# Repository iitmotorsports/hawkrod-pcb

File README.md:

View this project on [CADLAB.io](https://cadlab.io/project/25936). 

# hawkrod-pcb
The assets for the various PCBs and components of HawkRod

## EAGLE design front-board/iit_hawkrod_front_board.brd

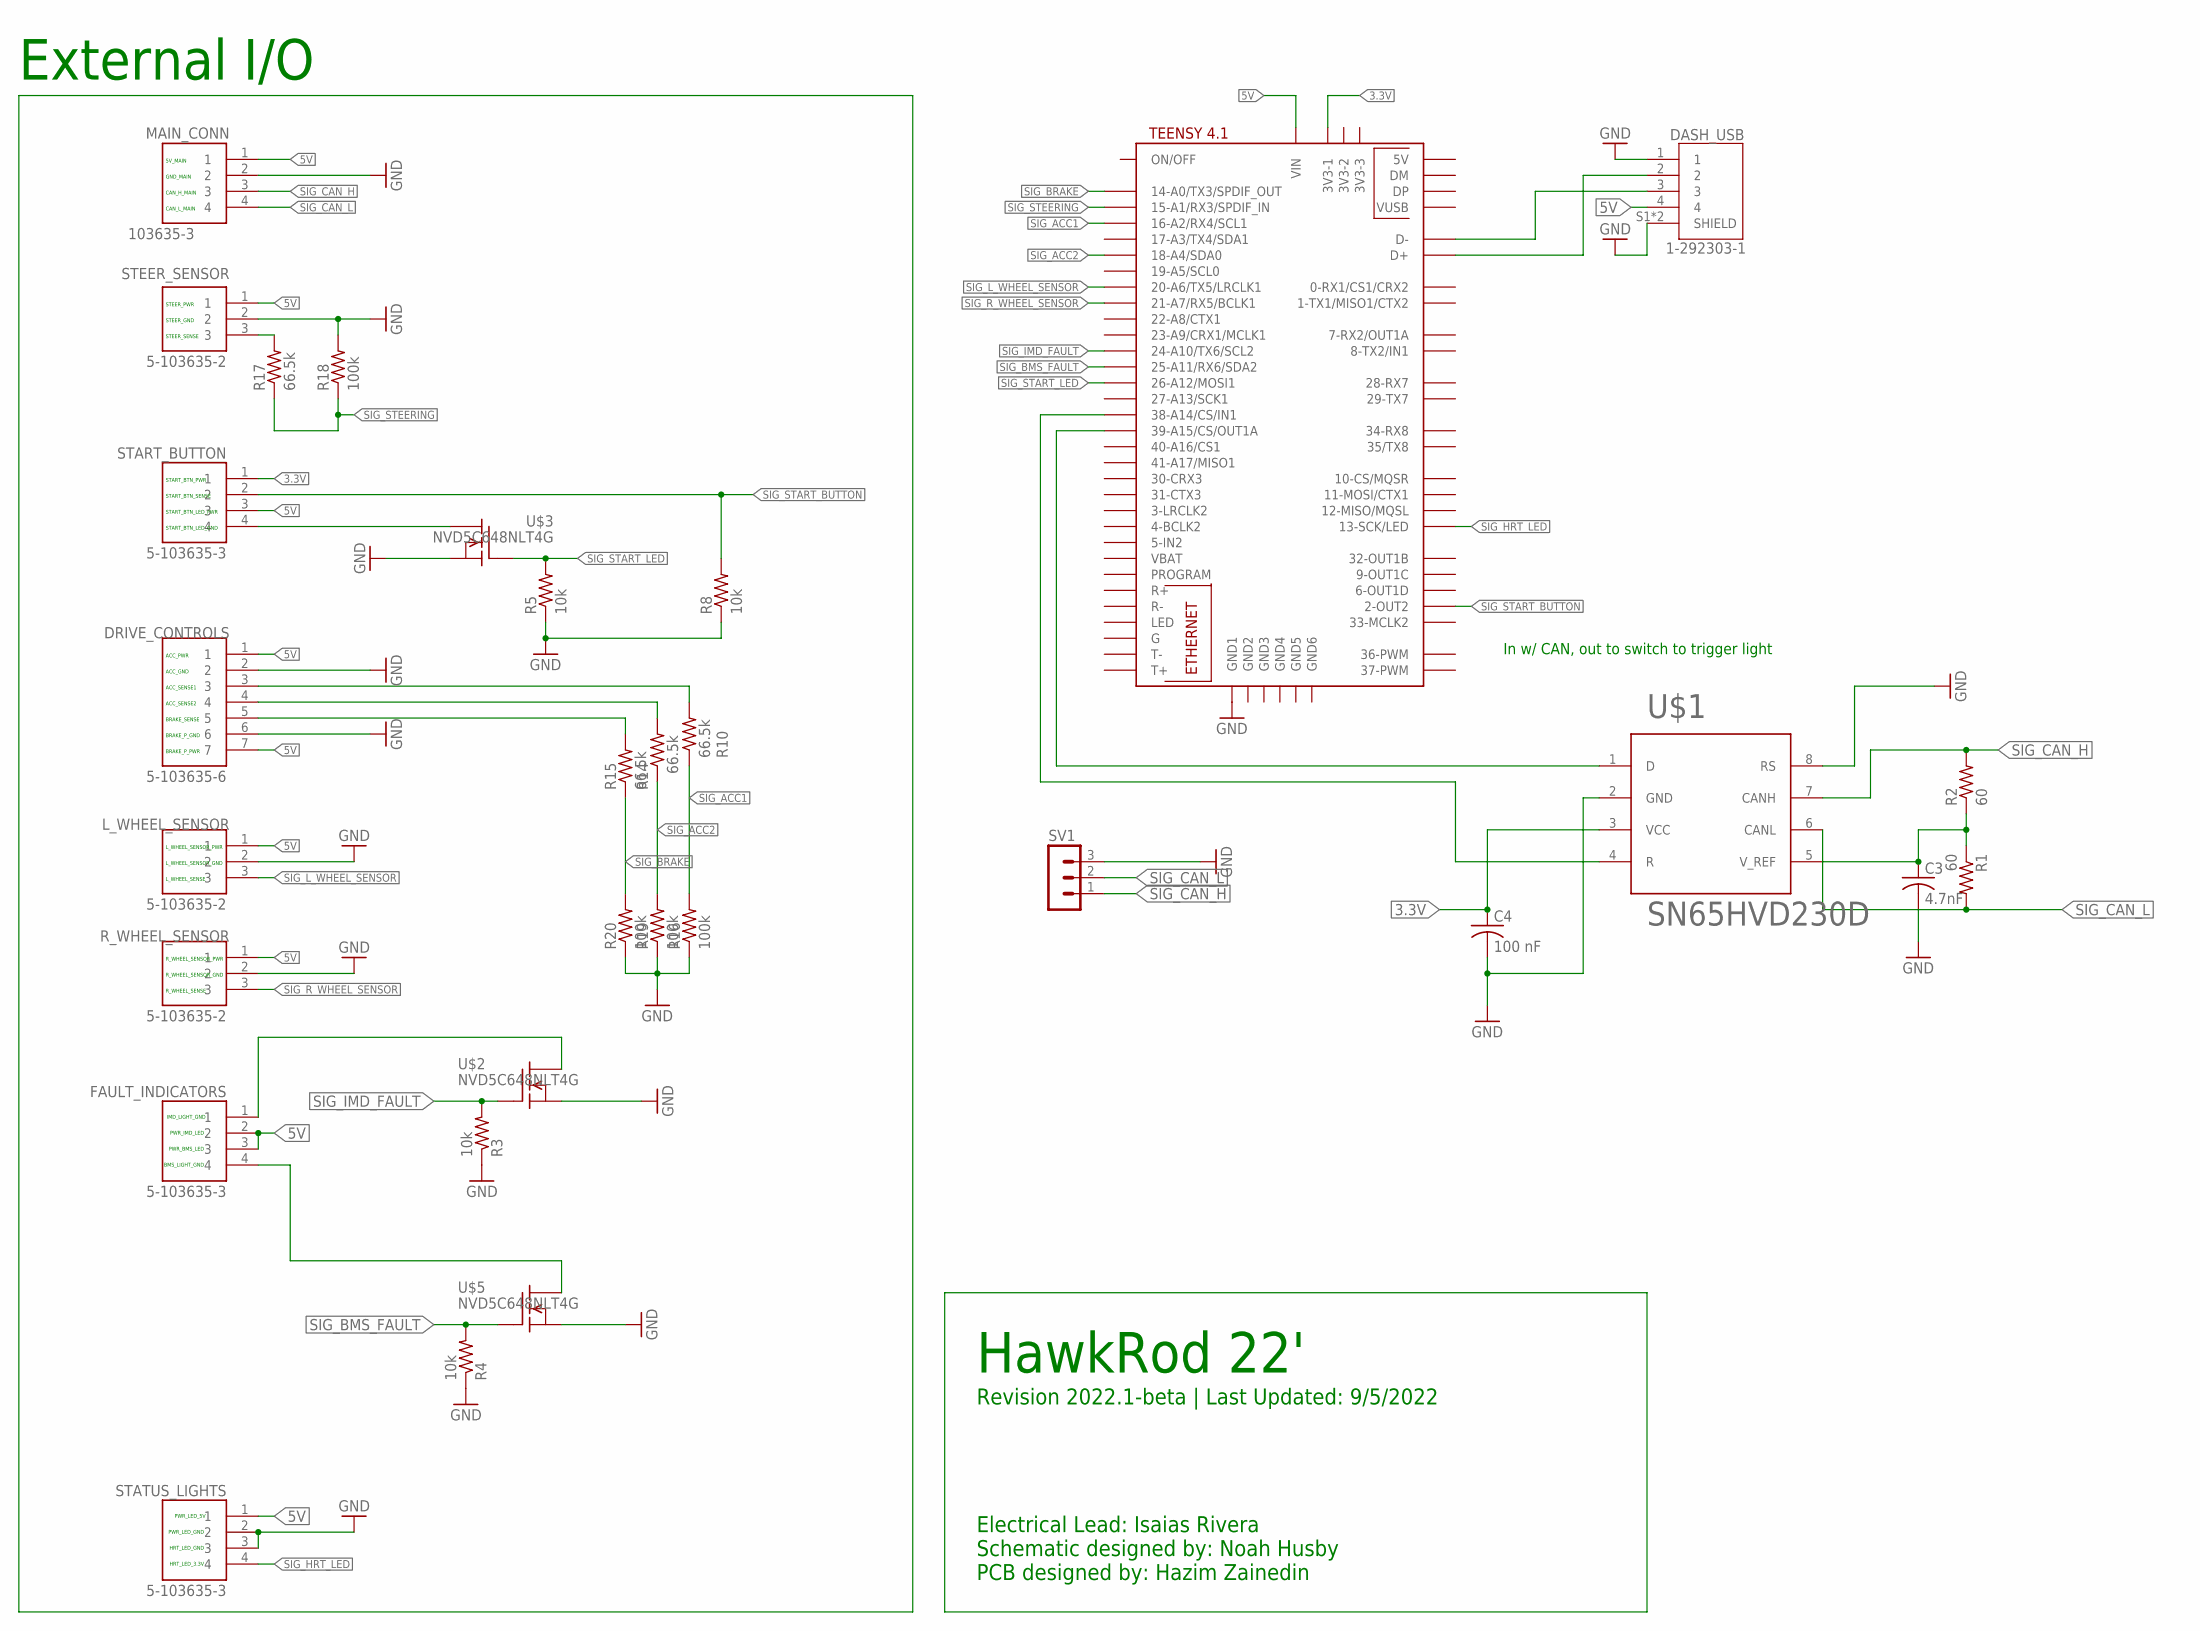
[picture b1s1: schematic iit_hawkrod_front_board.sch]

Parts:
C3: 4.7nF; C1206
C4: 100 nF; C1206
DASH_USB: 1-292303-1; TE_1-292303-1
DRIVE_CONTROLS: 5-103635-6; TE_5-103635-6
FAULT_INDICATORS: 5-103635-3; TE_5-103635-3
L_WHEEL_SENSOR: 5-103635-2; TE_5-103635-2
MAIN_CONN: 103635-3; TE_103635-3
R1, R2: 60; R1206
R3, R4, R5, R8: 10k; R1206
R10, R14, R15, R17: 66.5k; R1206
R16, R18, R19, R20: 100k; R1206
R_WHEEL_SENSOR: 5-103635-2; TE_5-103635-2
START_BUTTON: 5-103635-3; TE_5-103635-3
STATUS_LIGHTS: 5-103635-3; TE_5-103635-3
STEER_SENSOR: 5-103635-2; TE_5-103635-2
SV1: MA03-1
U$1: SN65HVD230D; R-PDSO-8
U$2, U$3, U$5: NVD5C648NLT4G; DPAK
U$6: TEENSY41

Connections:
3.3V: C4.1, START_BUTTON.1, U$1.3 (VCC), U$6.3V3-1
5V: DASH_USB.4, DRIVE_CONTROLS.1, DRIVE_CONTROLS.7, FAULT_INDICATORS.2, FAULT_INDICATORS.3, L_WHEEL_SENSOR.1, MAIN_CONN.1, R_WHEEL_SENSOR.1, START_BUTTON.3, STATUS_LIGHTS.1, STEER_SENSOR.1, U$6.VIN
GND: C3.2, C4.2, DASH_USB.1, DASH_USB.S1 (SHIELD), DASH_USB.S2 (SHIELD), DRIVE_CONTROLS.2, DRIVE_CONTROLS.6, L_WHEEL_SENSOR.2, MAIN_CONN.2, R3.1, R4.1, R5.1, R8.1, R16.1, R18.2, R19.1, R20.1, R_WHEEL_SENSOR.2, STATUS_LIGHTS.2, STATUS_LIGHTS.3, STEER_SENSOR.2, SV1.3, U$1.2 (GND), U$1.8 (RS), U$2.3 (S), U$3.3 (S), U$5.3 (S), U$6.GND1
unnamed: U$1.1 (D), U$6.39-A15/CS/OUT1A
unnamed: R2.2, U$1.7 (CANH)
unnamed: C3.1, R1.1, R2.1, U$1.5 (V_REF)
unnamed: FAULT_INDICATORS.1, U$2.4 (D)
unnamed: R1.2, U$1.6 (CANL)
unnamed: U$1.4 (R), U$6.38-A14/CS/IN1
unnamed: START_BUTTON.4, U$3.4 (D)
unnamed: FAULT_INDICATORS.4, U$5.4 (D)
unnamed: DRIVE_CONTROLS.3, R10.2
unnamed: DRIVE_CONTROLS.4, R14.2
unnamed: DASH_USB.3, U$6.D-
unnamed: DRIVE_CONTROLS.5, R15.2
unnamed: R17.2, STEER_SENSOR.3
unnamed: DASH_USB.2, U$6.D+
SIG_ACC1: R10.1, R16.2, U$6.16-A2/RX4/SCL1
SIG_ACC2: R14.1, R19.2, U$6.18-A4/SDA0
SIG_BMS_FAULT: R4.2, U$5.1 (G), U$6.25-A11/RX6/SDA2
SIG_BRAKE: R15.1, R20.2, U$6.14-A0/TX3/SPDIF_OUT
SIG_CAN_H: MAIN_CONN.3, SV1.1
SIG_CAN_L: MAIN_CONN.4, SV1.2
SIG_HRT_LED: STATUS_LIGHTS.4, U$6.13-SCK/LED
SIG_IMD_FAULT: R3.2, U$2.1 (G), U$6.24-A10/TX6/SCL2
SIG_L_WHEEL_SENSOR: L_WHEEL_SENSOR.3, U$6.20-A6/TX5/LRCLK1
SIG_R_WHEEL_SENSOR: R_WHEEL_SENSOR.3, U$6.21-A7/RX5/BCLK1
SIG_START_BUTTON: R8.2, START_BUTTON.2, U$6.2-OUT2
SIG_START_LED: R5.2, U$3.1 (G), U$6.26-A12/MOSI1
SIG_STEERING: R17.1, R18.1, U$6.15-A1/RX3/SPDIF_IN

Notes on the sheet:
PWR_IMD_LED
PWR_BMS_LED
IMD_LIGHT_GND
BMS_LIGHT_GND
In w/ CAN, out to switch to trigger light
GND_MAIN
5V_MAIN
CAN_H_MAIN
CAN_L_MAIN
STEER_PWR
STEER_GND
STEER_SENSE
START_BTN_PWR
START_BTN_LED_PWR
START_BTN_SENSE
START_BTN_LED_GND
ACC_PWR
ACC_GND
ACC_SENSE1
ACC_SENSE2
BRAKE_SENSE
BRAKE_P_GND
BRAKE_P_PWR
L_WHEEL_SENSOR_PWR
L_WHEEL_SENSOR_GND
L_WHEEL_SENSE
R_WHEEL_SENSOR_PWR
R_WHEEL_SENSOR_GND
R_WHEEL_SENSE
External I/O
HawkRod 22'
Revision 2022.1-beta | Last Updated: 9/5/2022
Electrical Lead: Isaias Rivera Schematic designed by: Noah Husby PCB designed by: Hazim Zainedin
PWR_LED_GND
HRT_LED_GND
PWR_LED_5V
HRT_LED_3.3V

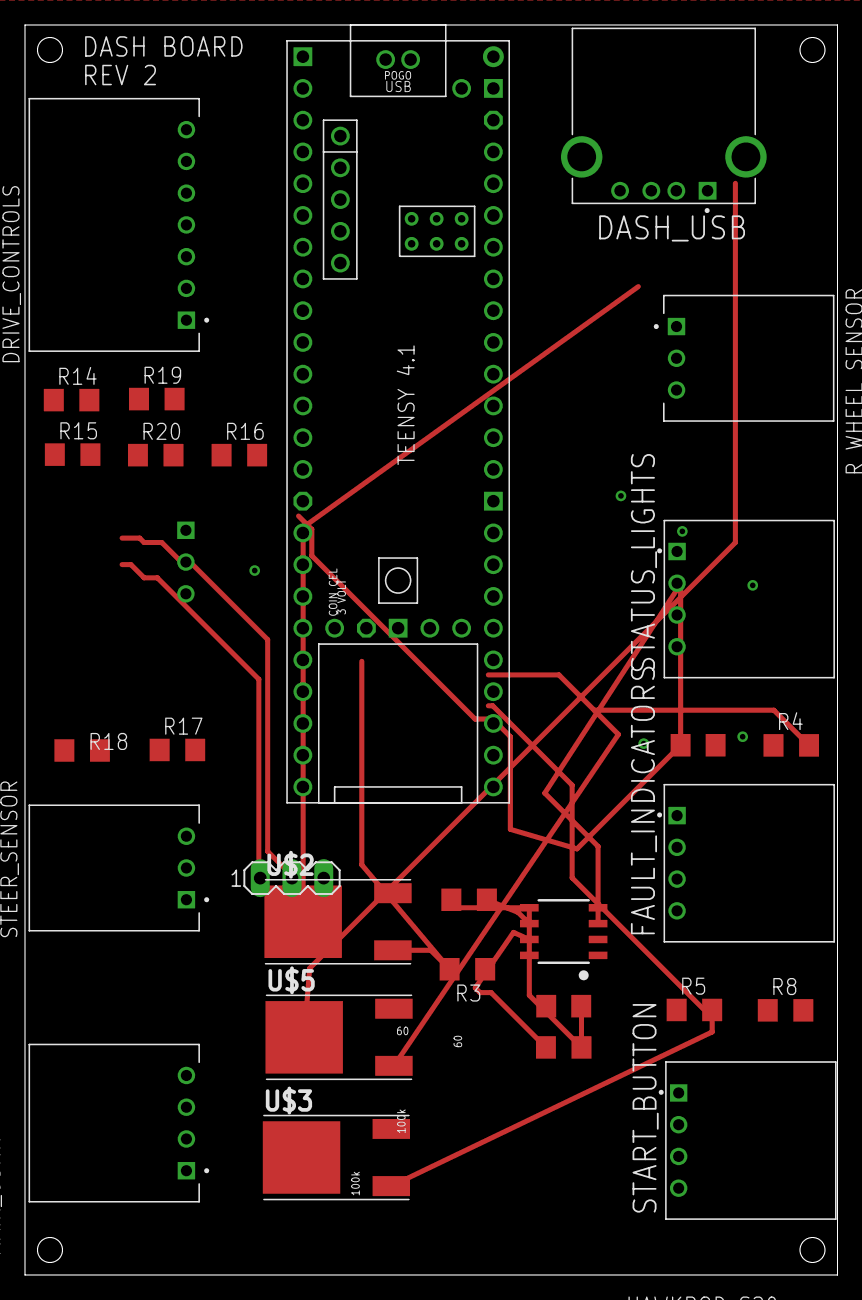
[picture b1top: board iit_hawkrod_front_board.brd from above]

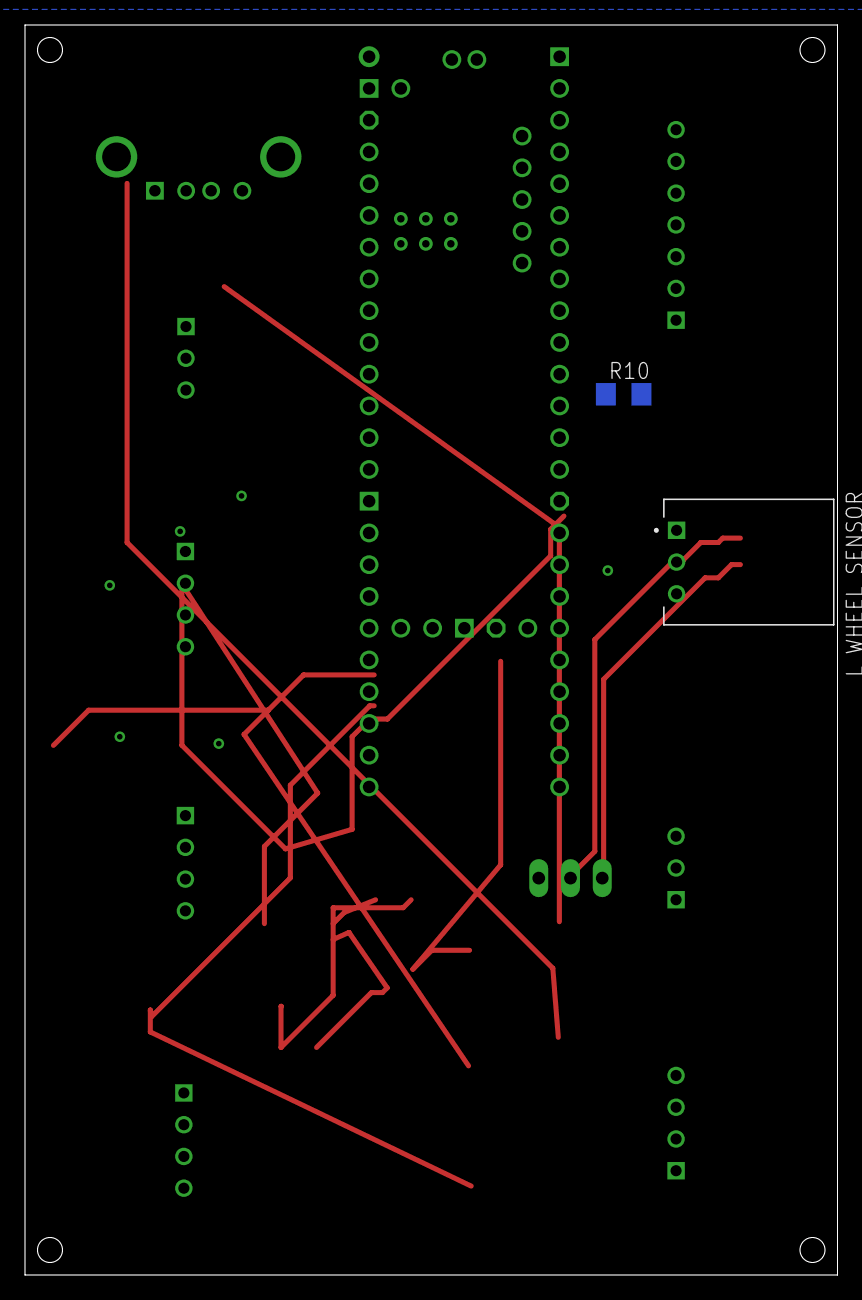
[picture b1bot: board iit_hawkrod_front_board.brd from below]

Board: 2 copper layers, 65.0 x 100.0 mm, 31 parts (2 on the bottom side), 30 nets.

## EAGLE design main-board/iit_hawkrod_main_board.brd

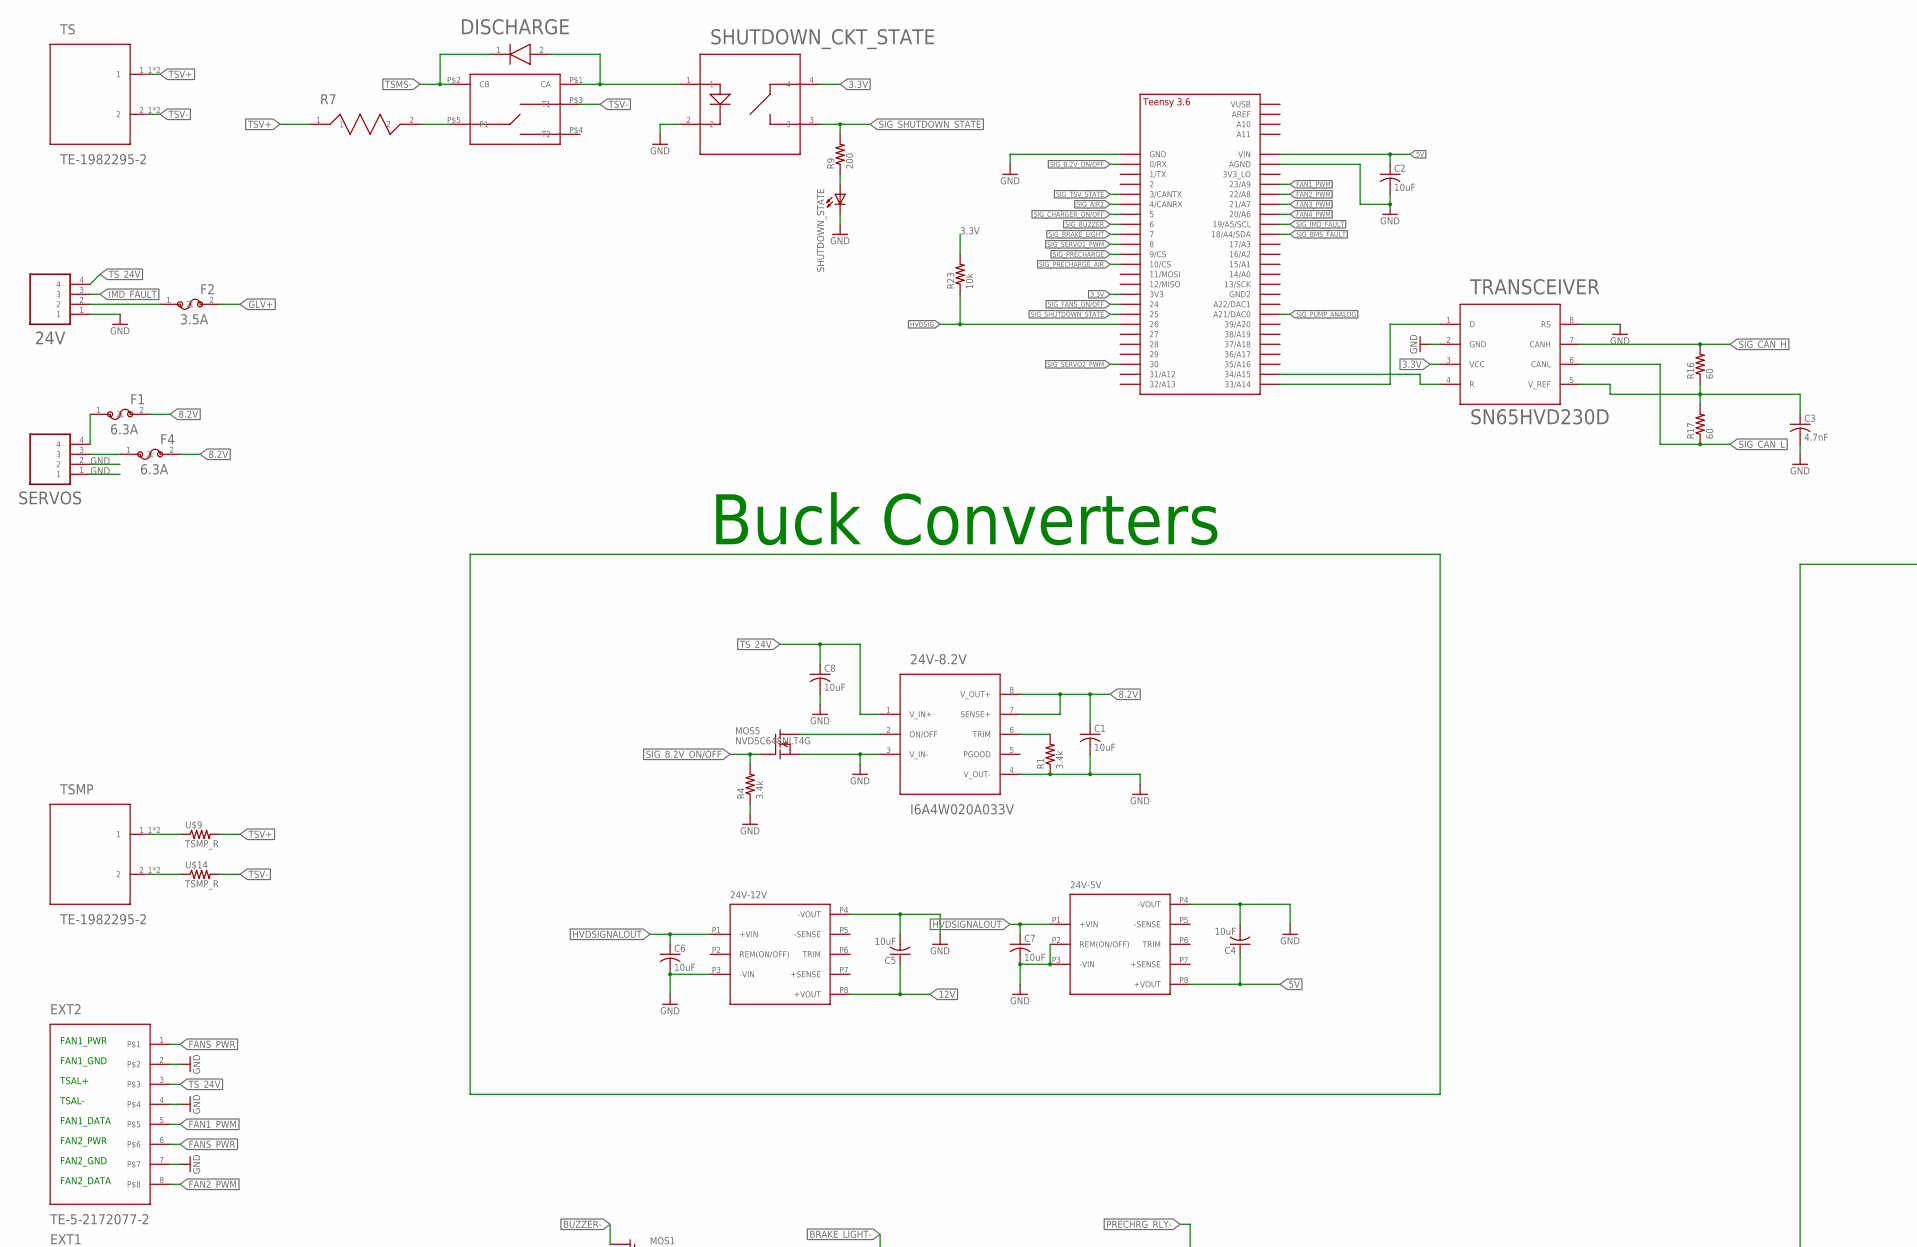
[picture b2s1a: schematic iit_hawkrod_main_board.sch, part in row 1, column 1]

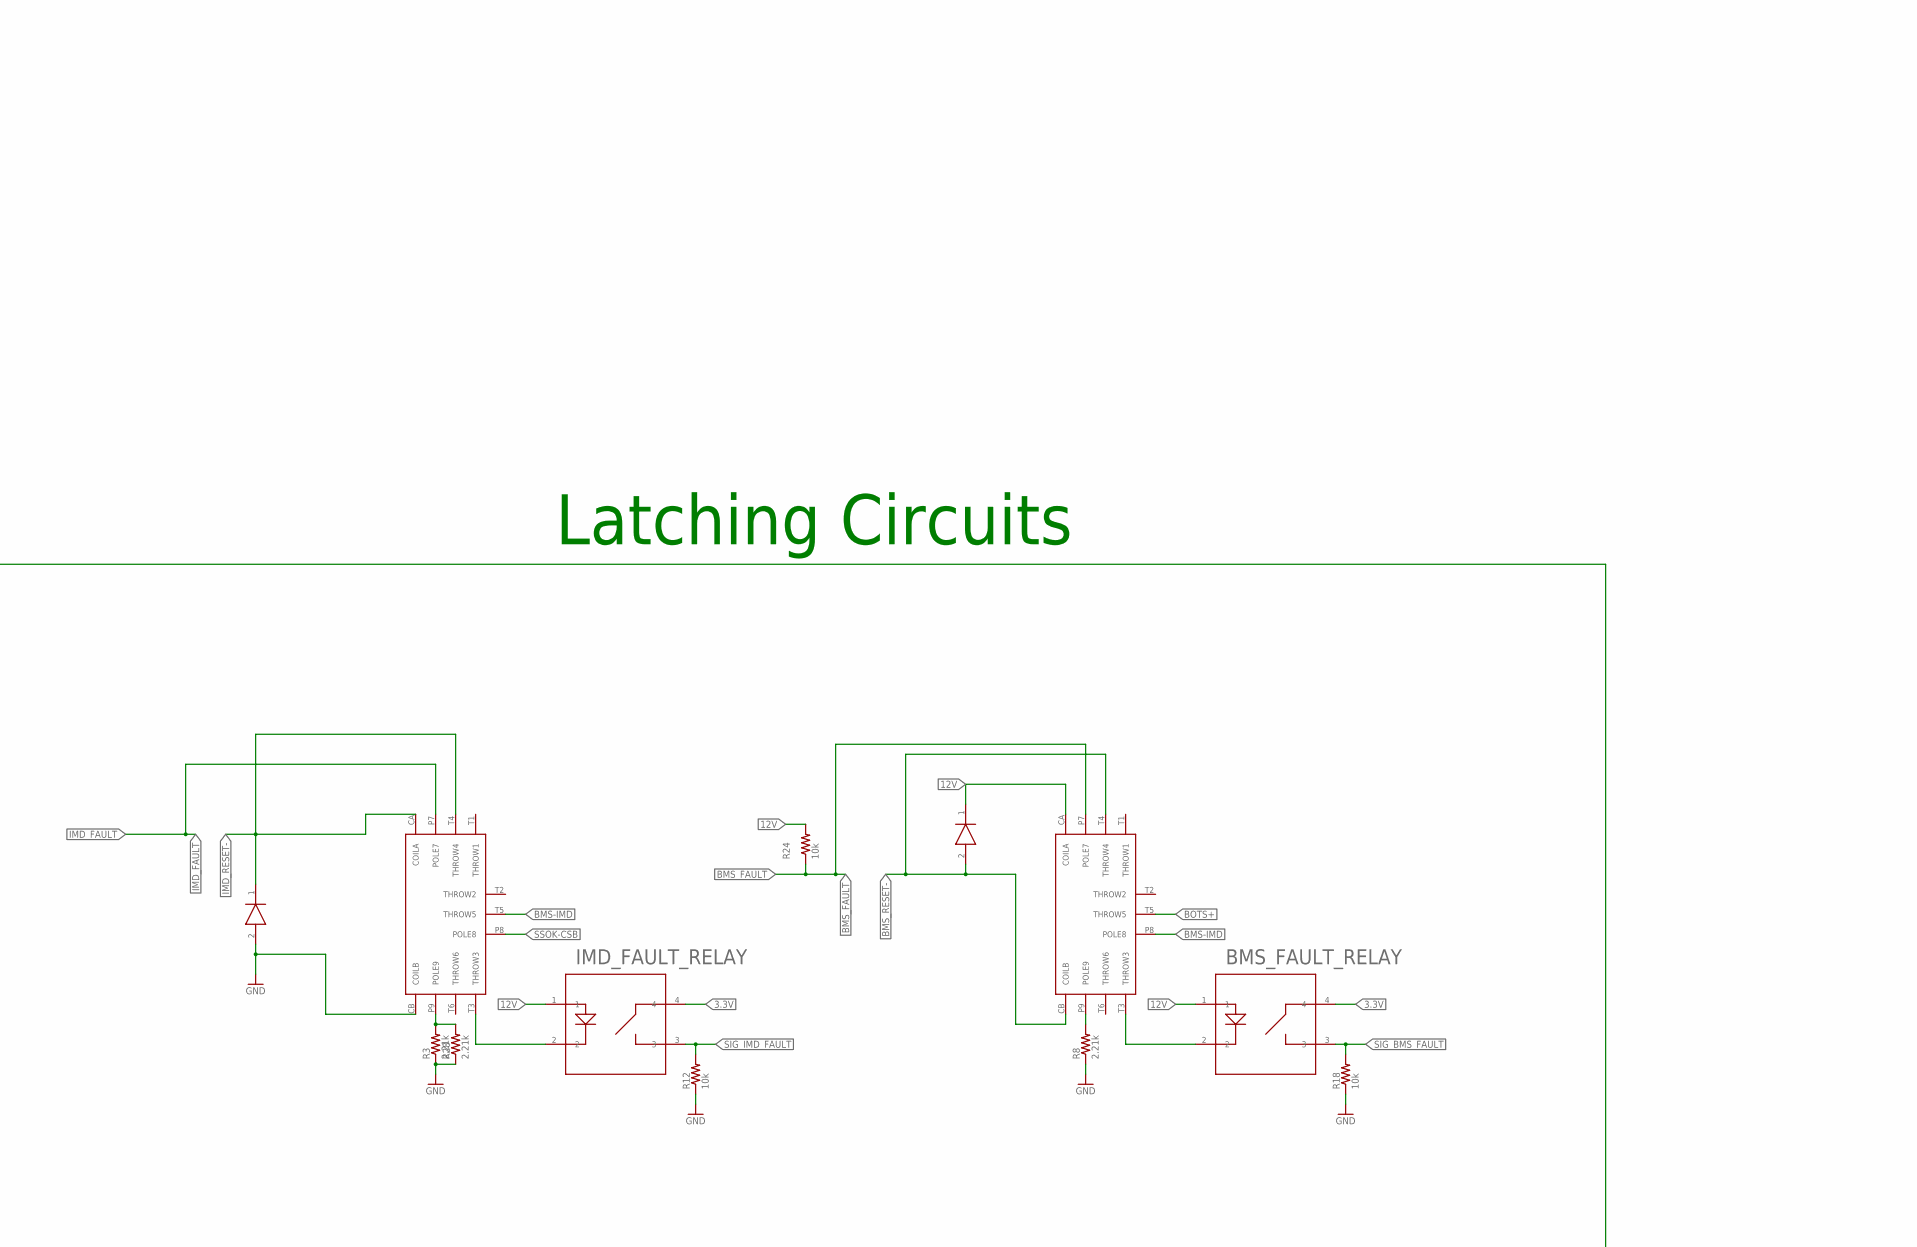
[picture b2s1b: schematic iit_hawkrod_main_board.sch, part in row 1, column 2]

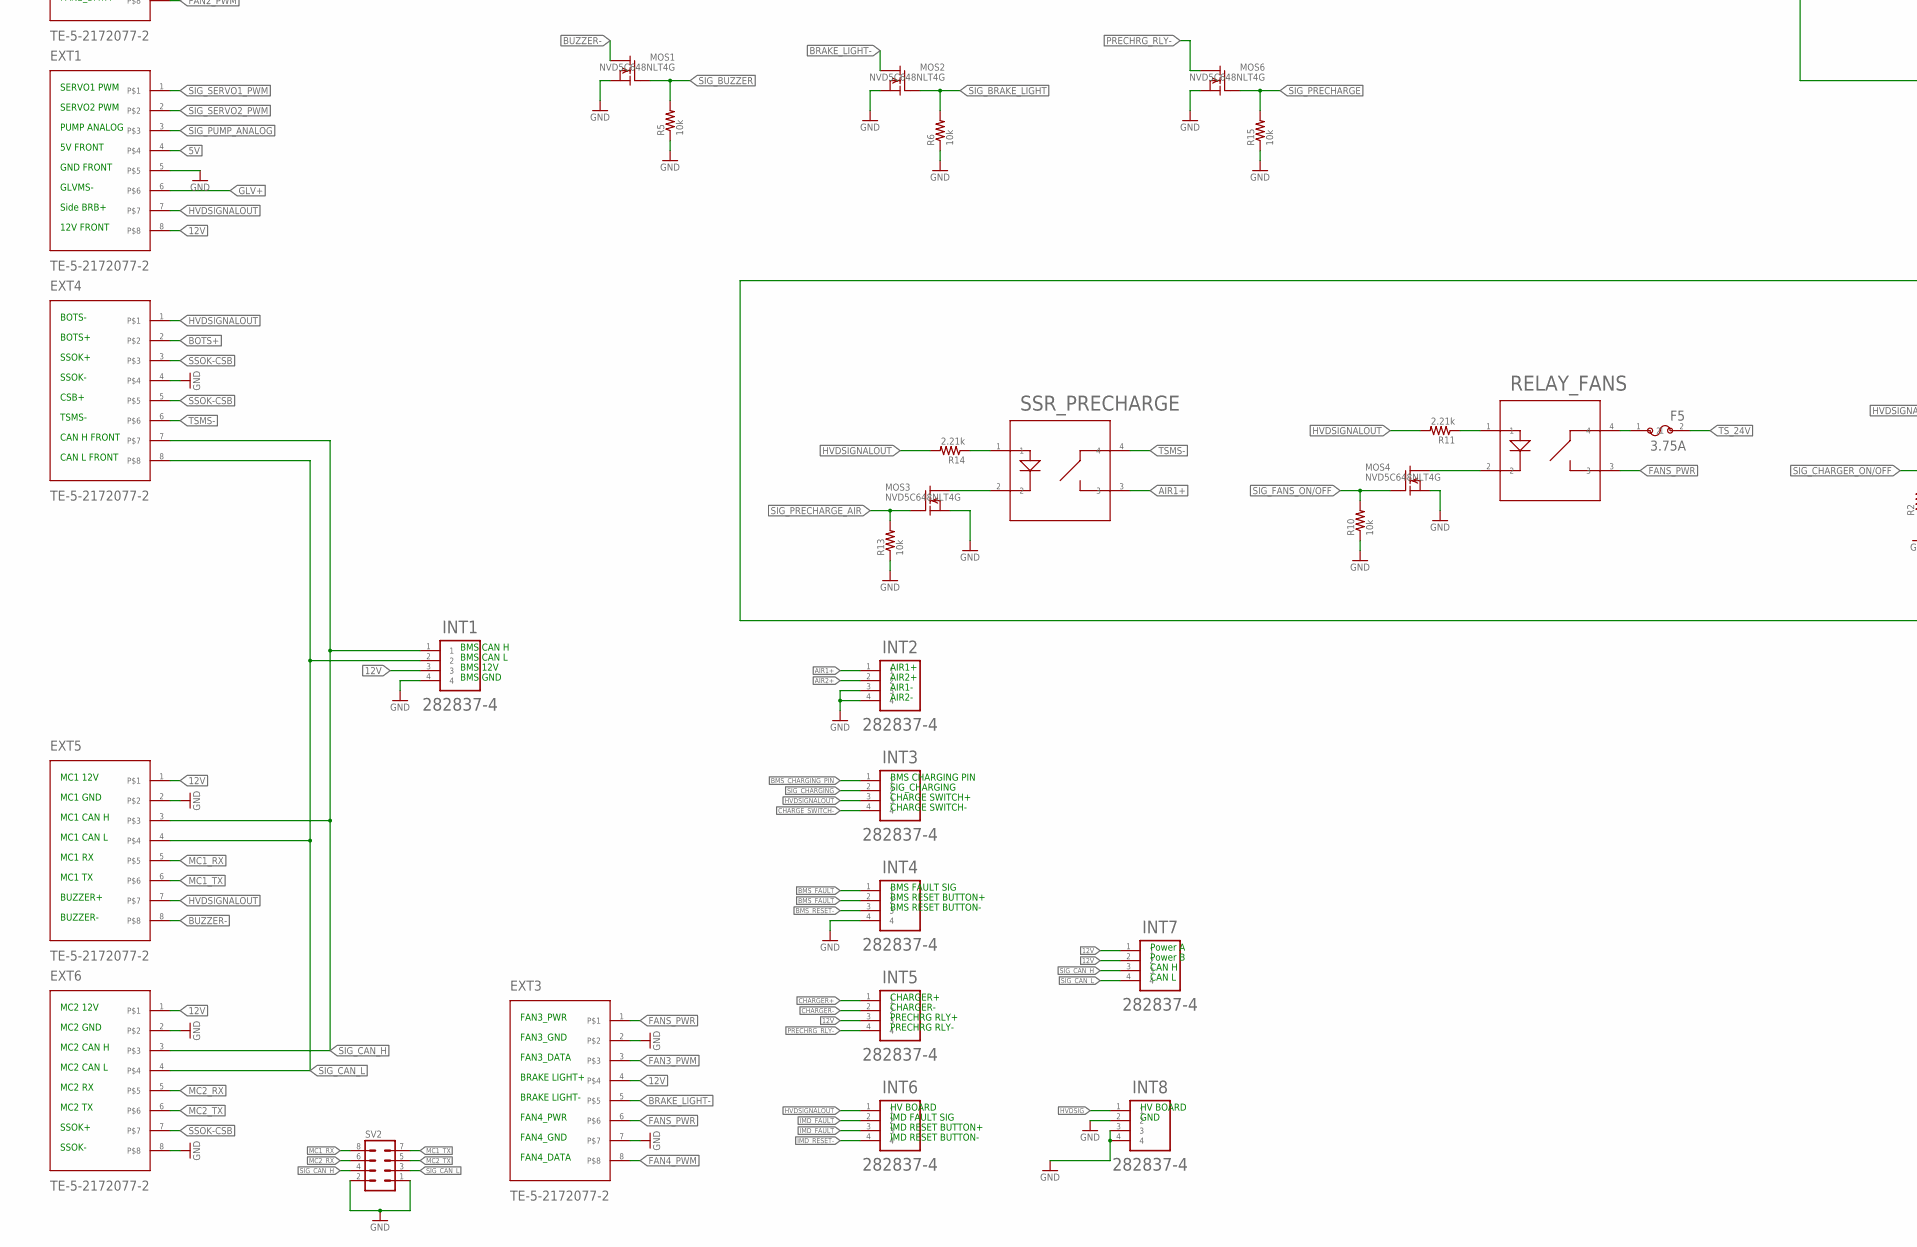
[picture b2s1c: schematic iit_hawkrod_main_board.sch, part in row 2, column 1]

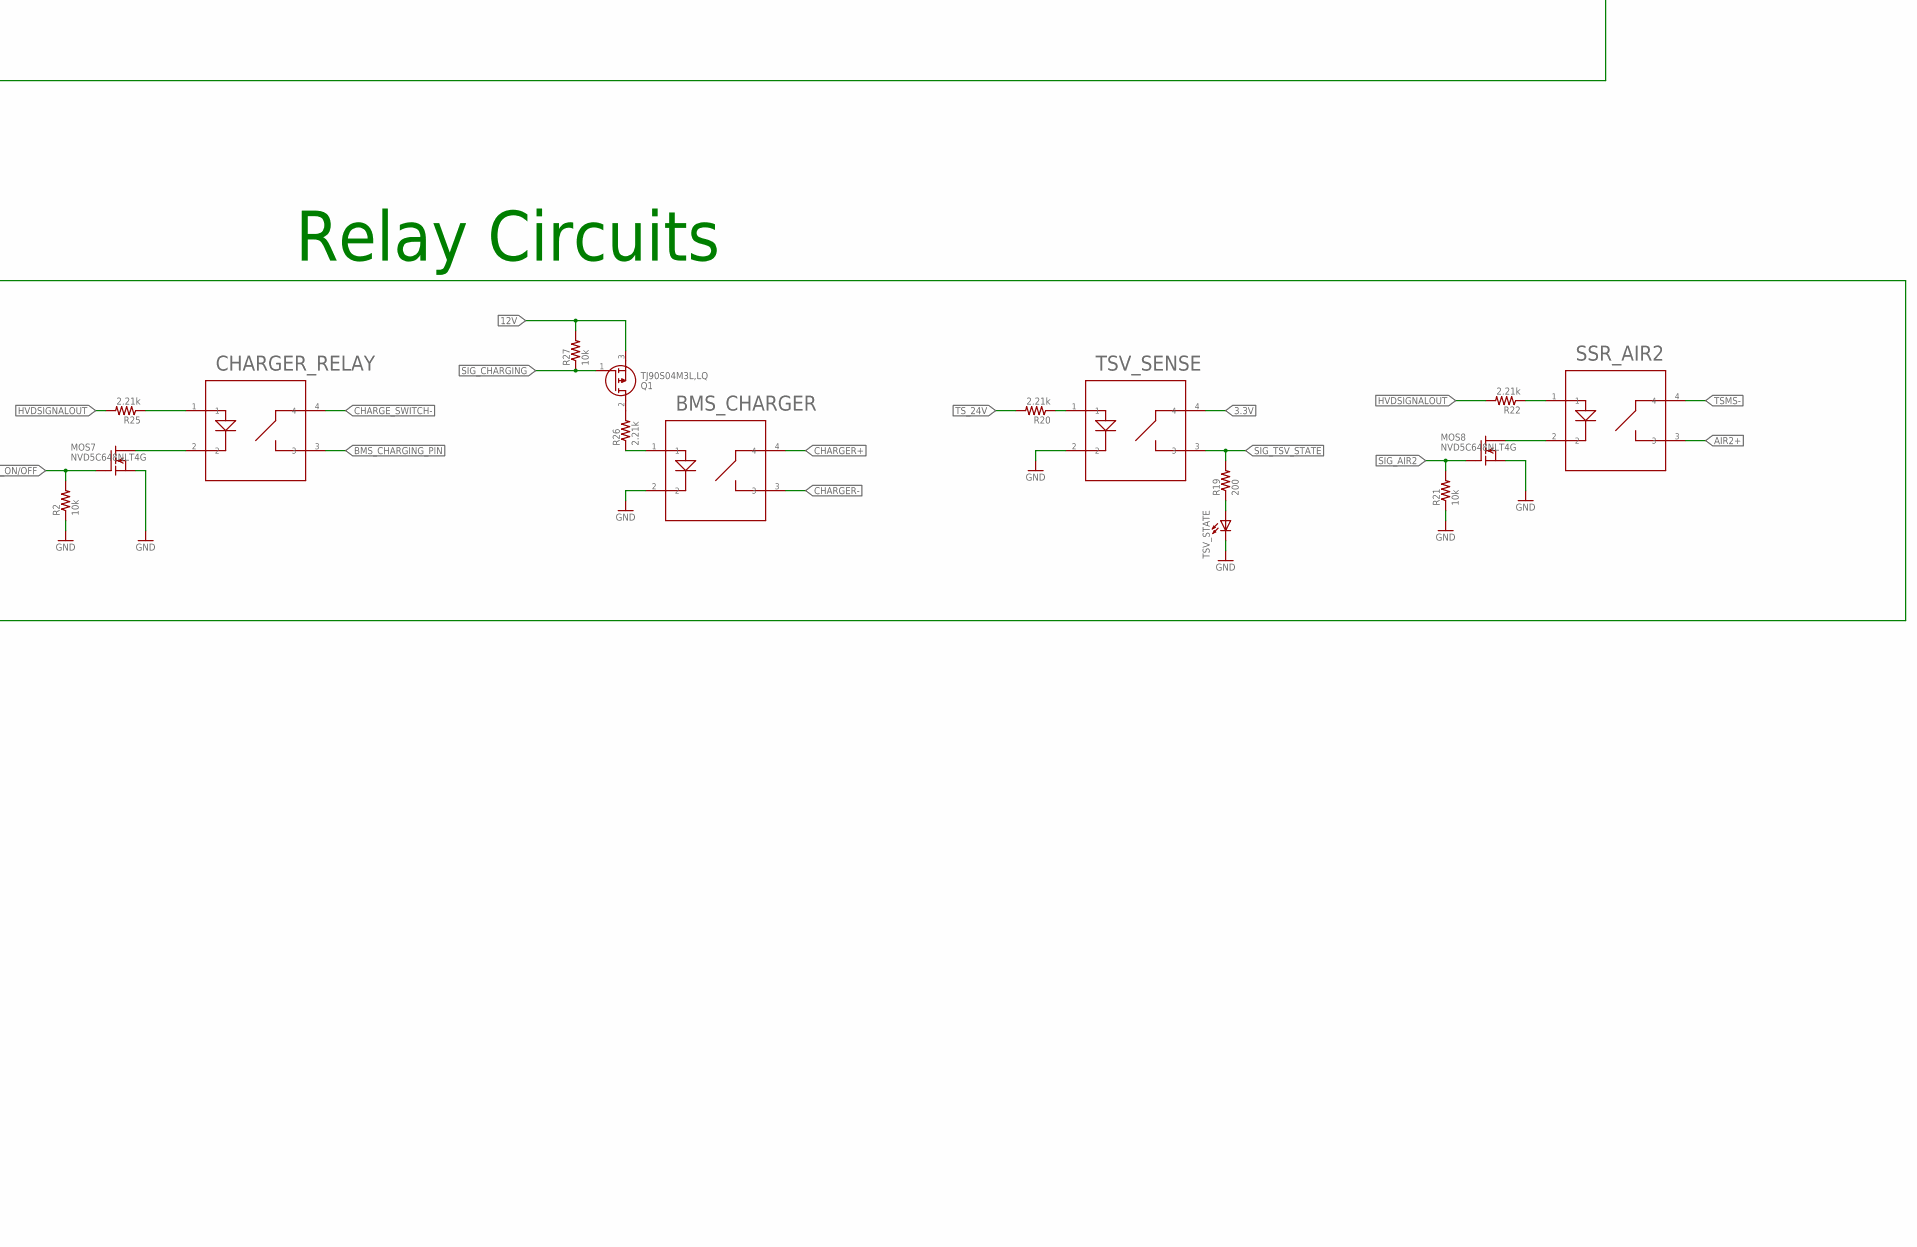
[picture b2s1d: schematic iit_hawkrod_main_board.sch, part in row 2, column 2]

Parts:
24V: 282837-4; TE_282837-4
24V-5V, 24V-12V: IRS-5/10-Q12NF-C
24V-8.2V: I6A4W020A033V
BMS_CHARGER: G3VM-61GR2; SOP4
BMS_FAULT_RELAY: G3VM-61GR2; SOP4
C1, C2, C4, C5, C6, C7, C8: 10uF; C1206
C3: 4.7nF; C1206
CHARGER_RELAY: G3VM-61GR2; SOP4
EXT1, EXT2, EXT3, EXT4, EXT5, EXT6: TE-5-2172077-2
F1, F4: 6.3A; SMD_FUSE_HOLDER
F2: 3.5A; SMD_FUSE_HOLDER
F5: 3.75A; SMD_FUSE_HOLDER
IMD_FAULT_RELAY: G3VM-61GR2; SOP4
INT1, INT2, INT3, INT4, INT5, INT6, INT7, INT8: 282837-4; TE_282837-4
MOS1, MOS2, MOS3, MOS4, MOS5, MOS6, MOS7, MOS8: NVD5C648NLT4G; DPAK
Q1: TJ90S04M3L,LQ; TJ90S04M3LLQ
R1, R4: 3.4k; R1206
R2, R10, R27: 10k; R1206
R3, R8, R11, R14, R20, R22, R25, R26, R28: 2.21k; R1206
R5, R6, R12, R13, R15, R18, R21, R23, R24: 10k; M1206
R7: HSA501K0J
R9, R19: 200; M1206
R16, R17: 60; R1206
RELAY_FANS: G3VM-61GR2; SOP4
SERVOS: 282837-4; TE_282837-4
SHUTDOWN_CKT_STATE: G3VM-61GR2; SOP4
SHUTDOWN_STATE: LEDCHIP-LED0805; CHIP-LED0805
SSR_AIR2: G3VM-61GR2; SOP4
SSR_PRECHARGE: G3VM-61GR2; SOP4
SV2: MA04-2
TEENSY_3.6: TEENSY_3.5/3.6_BASIC
TRANSCEIVER: SN65HVD230D; R-PDSO-8
TS: TE-1982295-2
TSMP: TE-1982295-2
TSV_SENSE: G3VM-61GR2; SOP4
TSV_STATE: LEDCHIP-LED0805; CHIP-LED0805
U$1: G2RL-1-HA
U$3, U$4, U$5: CS1M-E3/H; DO-214AC
U$6, U$7: 27E046_RELAY_MOUNT
U$9, U$14: TSMP_R

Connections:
3.3V: BMS_FAULT_RELAY.4, IMD_FAULT_RELAY.4, R23.2, SHUTDOWN_CKT_STATE.4, TEENSY_3.6.3V3, TRANSCEIVER.3 (VCC), TSV_SENSE.4
5V: 24V-5V.P8 (+VOUT), C2.1, C4.1, EXT1.4, TEENSY_3.6.VIN
8.2V: 24V-8.2V.7 (SENSE+), 24V-8.2V.8 (V_OUT+), C1.1, F1.2, F4.2
12V: 24V-12V.P8 (+VOUT), BMS_FAULT_RELAY.1, C5.1, EXT1.8, EXT3.4, EXT5.1, EXT6.1, IMD_FAULT_RELAY.1, INT1.3, INT5.3, INT7.1, INT7.2, Q1.3 (S), R24.2, R27.2, U$5.1 (2), U$7.CA (COILA)
AIR1+: INT2.1, SSR_PRECHARGE.3
AIR2+: INT2.2, SSR_AIR2.3
BMS-IMD: U$6.T5 (THROW5), U$7.P8 (POLE8)
BMS_CHARGING_PIN: CHARGER_RELAY.3, INT3.1
BMS_FAULT: INT4.1, INT4.2, R24.1, U$7.P7 (POLE7)
BMS_RESET-: INT4.3, U$5.2 (1), U$7.CB (COILB), U$7.T4 (THROW4)
BOTS+: EXT4.2, U$7.T5 (THROW5)
BRAKE_LIGHT-: EXT3.5, MOS2.4 (D)
BUZZER-: EXT5.8, MOS1.4 (D)
CHARGER+: BMS_CHARGER.4, INT5.1
CHARGER-: BMS_CHARGER.3, INT5.2
CHARGE_SWITCH-: CHARGER_RELAY.4, INT3.4
FAN1_PWM: EXT2.5, TEENSY_3.6.23/A9
FAN2_PWM: EXT2.8, TEENSY_3.6.22/A8
FAN3_PWM: EXT3.3, TEENSY_3.6.21/A7
FAN4_PWM: EXT3.8, TEENSY_3.6.20/A6
FANS_PWR: EXT2.1, EXT2.6, EXT3.1, EXT3.6, RELAY_FANS.3
GLV+: EXT1.6, F2.2
GND: 24V.1, 24V-5V.P2 (REM(ON/OFF)), 24V-5V.P3 (-VIN), 24V-5V.P4 (-VOUT), 24V-8.2V.3 (V_IN-), 24V-8.2V.4 (V_OUT-), 24V-12V.P3 (-VIN), 24V-12V.P4 (-VOUT), BMS_CHARGER.2, C1.2, C2.2, C3.2, C4.2, C5.2, C6.2, C7.2, C8.2, EXT1.5, EXT2.2, EXT2.4, EXT2.7, EXT3.2, EXT3.7, EXT4.4, EXT5.2, EXT6.2, EXT6.8, INT1.4, INT2.3, INT2.4, INT4.4, INT8.2, INT8.3, INT8.4, MOS1.3 (S), MOS2.3 (S), MOS3.3 (S), MOS4.3 (S), MOS5.3 (S), MOS6.3 (S), MOS7.3 (S), MOS8.3 (S), R1.1, R2.1, R3.1, R4.1, R5.1, R6.1, R8.1, R10.1, R12.1, R13.1, R15.1, R18.1, R21.1, R28.1, SERVOS.1, SERVOS.2, SHUTDOWN_CKT_STATE.2, SHUTDOWN_STATE.C, SV2.1, SV2.2, TEENSY_3.6.AGND, TEENSY_3.6.GND, TRANSCEIVER.2 (GND), TRANSCEIVER.8 (RS), TSV_SENSE.2, TSV_STATE.C, U$4.2 (1), U$6.CB (COILB)
HVDSIG: INT8.1, R23.1, TEENSY_3.6.26
HVDSIGNALOUT: 24V-5V.P1 (+VIN), 24V-12V.P1 (+VIN), C6.1, C7.1, EXT1.7, EXT4.1, EXT5.7, INT3.3, INT6.1, R11.2, R14.2, R22.2, R25.2
IMD_FAULT: 24V.3, INT6.2, INT6.3, U$6.P7 (POLE7)
IMD_RESET-: INT6.4, U$4.1 (2), U$6.CA (COILA), U$6.T4 (THROW4)
MC1_RX: EXT5.5, SV2.8
MC1_TX: EXT5.6, SV2.7
MC2_RX: EXT6.5, SV2.6
MC2_TX: EXT6.6, SV2.5
unnamed: 24V-8.2V.6 (TRIM), R1.2
unnamed: 24V-8.2V.2 (ON/OFF), MOS5.4 (D)
unnamed: 24V.2, F2.1
unnamed: MOS4.4 (D), RELAY_FANS.2
unnamed: TSMP.1_1 (1), TSMP.1_2 (1), U$9.T1 (1)
unnamed: TSMP.2_1 (2), TSMP.2_2 (2), U$14.T1 (1)
unnamed: R7.2, U$1.P$5 (P1)
unnamed: R11.1, RELAY_FANS.1
unnamed: SHUTDOWN_CKT_STATE.1, U$1.P$1 (CA), U$3.2 (1)
unnamed: CHARGER_RELAY.2, MOS7.4 (D)
unnamed: R3.2, R28.2, U$6.P9 (POLE9)
unnamed: F1.1, SERVOS.4
unnamed: F4.1, SERVOS.3
unnamed: F5.1, RELAY_FANS.4
unnamed: R14.1, SSR_PRECHARGE.1
unnamed: R8.2, U$7.P9 (POLE9)
unnamed: MOS3.4 (D), SSR_PRECHARGE.2
unnamed: R9.1, SHUTDOWN_STATE.A
unnamed: R19.1, TSV_STATE.A
unnamed: TEENSY_3.6.34/A15, TRANSCEIVER.4 (R)
unnamed: IMD_FAULT_RELAY.2, U$6.T3 (THROW3)
unnamed: R20.1, TSV_SENSE.1
unnamed: BMS_FAULT_RELAY.2, U$7.T3 (THROW3)
unnamed: R22.1, SSR_AIR2.1
unnamed: TEENSY_3.6.33/A14, TRANSCEIVER.1 (D)
unnamed: C3.1, R16.1, R17.2, TRANSCEIVER.5 (V_REF)
unnamed: MOS8.4 (D), SSR_AIR2.2
unnamed: Q1.2 (D), R26.2
unnamed: CHARGER_RELAY.1, R25.1
unnamed: BMS_CHARGER.1, R26.1
PRECHRG_RLY-: INT5.4, MOS6.4 (D)
SIG_8.2V_ON/OFF: MOS5.1 (G), R4.2, TEENSY_3.6.0/RX
SIG_AIR2: MOS8.1 (G), R21.2, TEENSY_3.6.4/CANRX
SIG_BMS_FAULT: BMS_FAULT_RELAY.3, R18.2, TEENSY_3.6.18/A4/SDA
SIG_BRAKE_LIGHT: MOS2.1 (G), R6.2, TEENSY_3.6.7
SIG_BUZZER: MOS1.1 (G), R5.2, TEENSY_3.6.6
SIG_CAN_H: EXT4.7, EXT5.3, EXT6.3, INT1.1, INT7.3, R16.2, SV2.4, TRANSCEIVER.7 (CANH)
SIG_CAN_L: EXT4.8, EXT5.4, EXT6.4, INT1.2, INT7.4, R17.1, SV2.3, TRANSCEIVER.6 (CANL)
SIG_CHARGER_ON/OFF: MOS7.1 (G), R2.2, TEENSY_3.6.5
SIG_CHARGING: INT3.2, Q1.1 (G), R27.1
SIG_FANS_ON/OFF: MOS4.1 (G), R10.2, TEENSY_3.6.24
SIG_IMD_FAULT: IMD_FAULT_RELAY.3, R12.2, TEENSY_3.6.19/A5/SCL
SIG_PRECHARGE: MOS6.1 (G), R15.2, TEENSY_3.6.9/CS
SIG_PRECHARGE_AIR: MOS3.1 (G), R13.2, TEENSY_3.6.10/CS
SIG_PUMP_ANALOG: EXT1.3, TEENSY_3.6.21/DAC0 (A21/DAC0)
SIG_SERVO1_PWM: EXT1.1, TEENSY_3.6.8
SIG_SERVO2_PWM: EXT1.2, TEENSY_3.6.30
SIG_SHUTDOWN_STATE: R9.2, SHUTDOWN_CKT_STATE.3, TEENSY_3.6.25
SIG_TSV_STATE: R19.2, TEENSY_3.6.3/CANTX, TSV_SENSE.3
SSOK-CSB: EXT4.3, EXT4.5, EXT6.7, U$6.P8 (POLE8)
TSMS-: EXT4.6, SSR_AIR2.4, SSR_PRECHARGE.4, U$1.P$2 (CB), U$3.1 (2)
TSV+: R7.1, TS.1_1 (1), TS.1_2 (1), U$9.T2 (2)
TSV-: TS.2_1 (2), TS.2_2 (2), U$1.P$3 (T1), U$14.T2 (2)
TS_24V: 24V.4, 24V-8.2V.1 (V_IN+), C8.1, EXT2.3, F5.2, R20.2

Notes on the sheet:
TSAL+
TSAL-
DISCHARGE
GLVMS-
Side BRB+
BOTS-
BOTS+
SSOK+
SSOK-
CSB+
AIR1-
AIR2-
BMS 12V
BMS GND
MC1 12V
MC2 12V
MC1 GND
MC2 GND
MC1 CAN H
MC1 CAN L
MC1 RX
MC1 TX
MC2 CAN H
MC2 CAN L
MC2 RX
MC2 TX
BMS CAN H
BMS CAN L
CAN H FRONT
CAN L FRONT
FAN1_PWR
FAN2_PWR
FAN1_GND
FAN2_GND
FAN2_DATA
FAN1_DATA
FAN3_PWR
FAN4_PWR
FAN3_GND
FAN4_GND

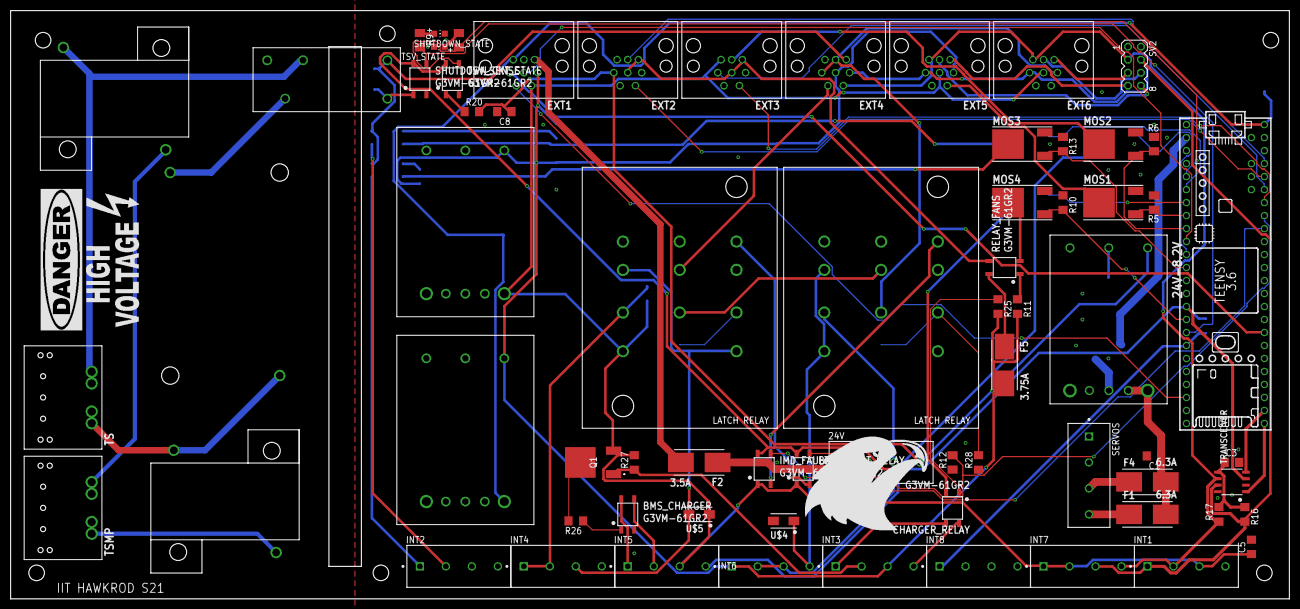
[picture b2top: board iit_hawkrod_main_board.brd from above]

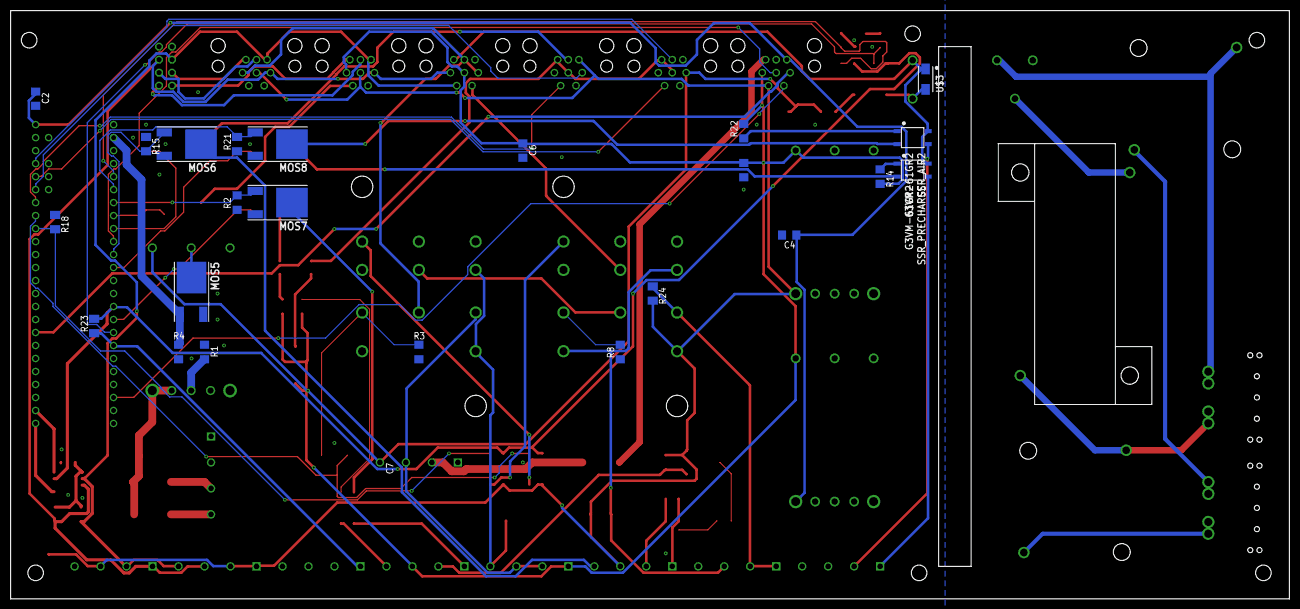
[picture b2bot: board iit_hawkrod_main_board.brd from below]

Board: 2 copper layers, 250.0 x 115.0 mm, 92 parts (24 on the bottom side), 85 nets.

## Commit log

2022-09-06 Reworked front-board schematic. Added libraries
2022-09-06 Backlink to CADLAB.io has been added.
2022-09-08 Add Status Lights
2022-09-09 Add USB
2022-09-09 Layout_Pre
